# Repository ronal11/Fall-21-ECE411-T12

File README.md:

# Fall-21-ECE411-
Repository for ECE411 practicum project.

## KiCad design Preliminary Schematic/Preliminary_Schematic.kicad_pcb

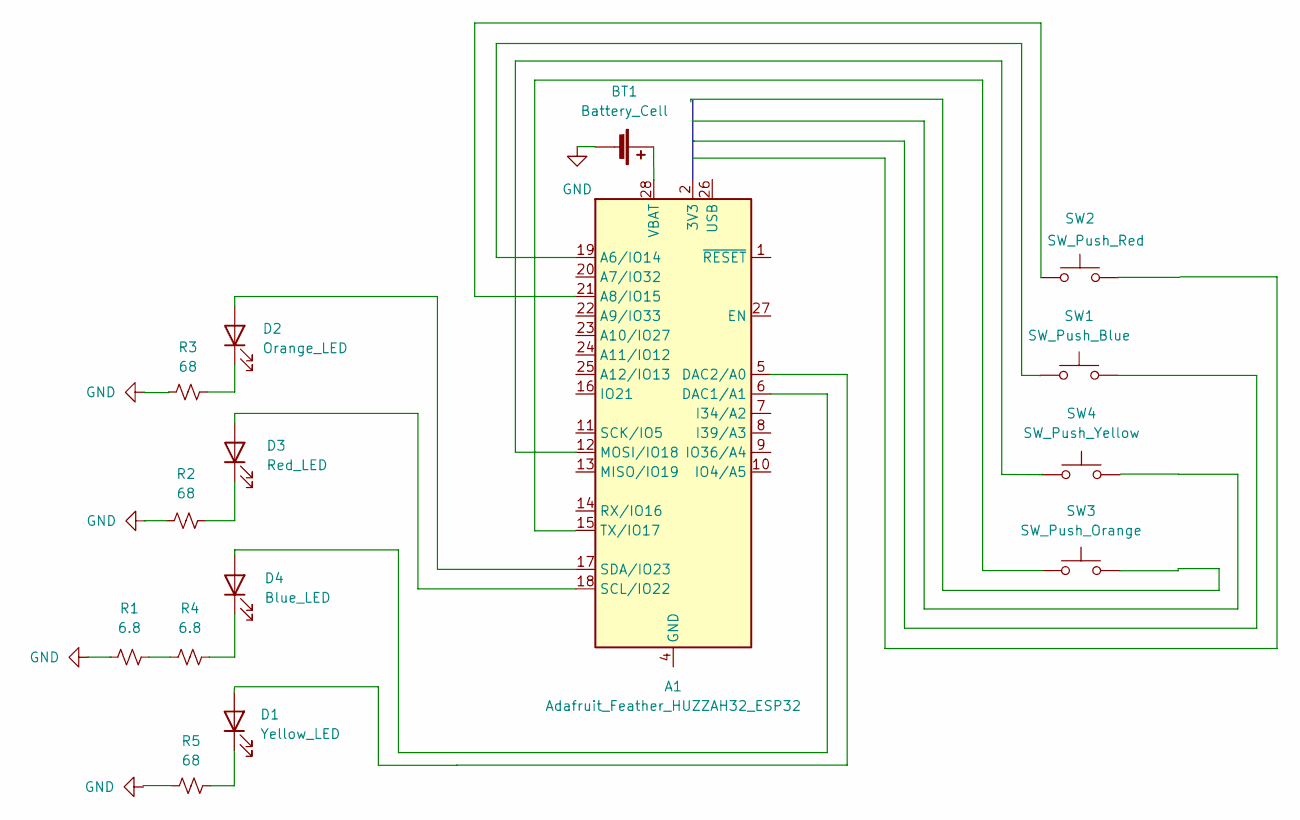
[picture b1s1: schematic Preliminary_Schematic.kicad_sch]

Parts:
A1: Adafruit_Feather_HUZZAH32_ESP32; Adafruit_Feather
BT1: Battery_Cell; BatteryHolder_Keystone_2479_3xAAA
D1: Yellow_LED; LED_0201_0603Metric
D2: Orange_LED; LED_0201_0603Metric
D3: Red_LED; LED_0201_0603Metric
D4: Blue_LED; LED_0201_0603Metric
R1, R4: 6.8; R_0805_2012Metric_Pad1.20x1.40mm_HandSolder
R2, R3, R5: 68; R_0805_2012Metric_Pad1.20x1.40mm_HandSolder
SW1: SW_Push_Blue; SW_SPST_B3U-1000P
SW2: SW_Push_Red; SW_SPST_B3U-1000P
SW3: SW_Push_Orange; SW_SPST_B3U-1000P
SW4: SW_Push_Yellow; SW_SPST_B3U-1000P

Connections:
unnamed: A1.6 (DAC1/A1), D4.2 (A)
unnamed: A1.17 (SDA/IO23), D2.2 (A)
unnamed: A1.18 (SCL/IO22), D3.2 (A)
unnamed: D1.1 (K), R5.2
unnamed: D2.1 (K), R3.2
unnamed: D3.1 (K), R2.2
unnamed: D4.1 (K), R4.2
unnamed: R1.2, R4.1

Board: 2 copper layers, 15 parts (0 on the bottom side), 8 nets, no tracks yet.

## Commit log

2021-10-20 Simon Says level 1 block diagram
    1st draft, feedback welcome.
2021-10-29 Added Week 5 HW breadboard prototype and schematic
2021-11-04 Base code
    Base code for pushbuttons and LEDs.
2021-11-04 TestChange
2021-11-04 Our tentative Project Schedule
2021-11-04 Base KiCAD schematic with 4 push-buttons and 4 LEDs
2021-11-05 Some of the wires seems to not want to snap on pins in the schematic, for that reason some of the wires aren't showing on the pcb layout.
2021-11-05 Footprints assigned to circuit components. Now layout generates without errors.
2021-11-11 added BOM
2021-11-17 Updated battery socket type, two pins now "fits well with Arduino batteries. I also created PCB traces. NOTE* Huzzah32's ground pin is not connected to a trace yet.
2021-11-18 Final edit - Reconfigured pins - replaced LEDs - removed connector pin-header
2021-11-18 Added Revision tag and date
2021-11-18 Osh park instruction part 1
2021-11-19 Uncommented simon says code
2021-11-21 many changes check description
    o buttons are now interpreted as active low
    o added a separate function to handle user vs. generated comparison
    o changed void loop to start only upon user pressing red led button, even after getting inputting an correct sequence
    o restructured get_sequence function
    o added comments
    o fixed bug where last led input stays on
2021-11-23 changed code to work with active high buttons
2021-11-28 added gamemodes and cleaned up code
2021-12-09 prototype circuit v2
2021-12-09 Prototype Board V1
2021-12-09 organization
2021-12-09 Add files via upload
    final version of Simon Says code
